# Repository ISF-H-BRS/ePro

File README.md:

# ePro: Secret Messages

## Introduction
ePro (short for entry-level project) was a series of introduction courses offered by Bonn-Rhein-Sieg University of Applied Sciences starting in 2010.

One of these courses, named "Secret Messages", aimed to give first-semester students a practical introduction to the field of data transmission, from the most low-level concepts, such as logical voltage levels, over bus systems like UART, SPI and I²C up to higher-level concepts, such as protocol stacks and data encryption.

This repository contains schematics, PCB layout and firmware for a circuit board originally developed during an internship project in the summer of 2010 to support this course beginning later that year. These devices, based on an ATmega32 microcontroller, can communicate over any of the three aforementioned interfaces and exchange messages using a very simple encryption scheme. All signals are exposed via pin headers for analysis by means of oscilloscope and/or bus sniffer.

The message to be transmitted can be selected from a built-in database of famous quotations through a pin-protected administration menu where also the encryption key can be set. The goal of the project was for every team to analyze the data transmitted over the chosen interface, decipher the message and document their findings along the way.

Unfortunately the ePro courses were canceled with the introduction of a new curriculum some years ago. This repository is provided in the hope that the circuit boards developed back in 2010 might still find some use in similar academic projects in the future.

## License
The source code for the firmware is licensed under the terms of the GNU General Public License (GPL). The schematics and layout files are licensed under the terms of the Creative Commons Attribution-ShareAlike International Public License (CC BY-SA). See COPYING in the respective subdirectories for details.

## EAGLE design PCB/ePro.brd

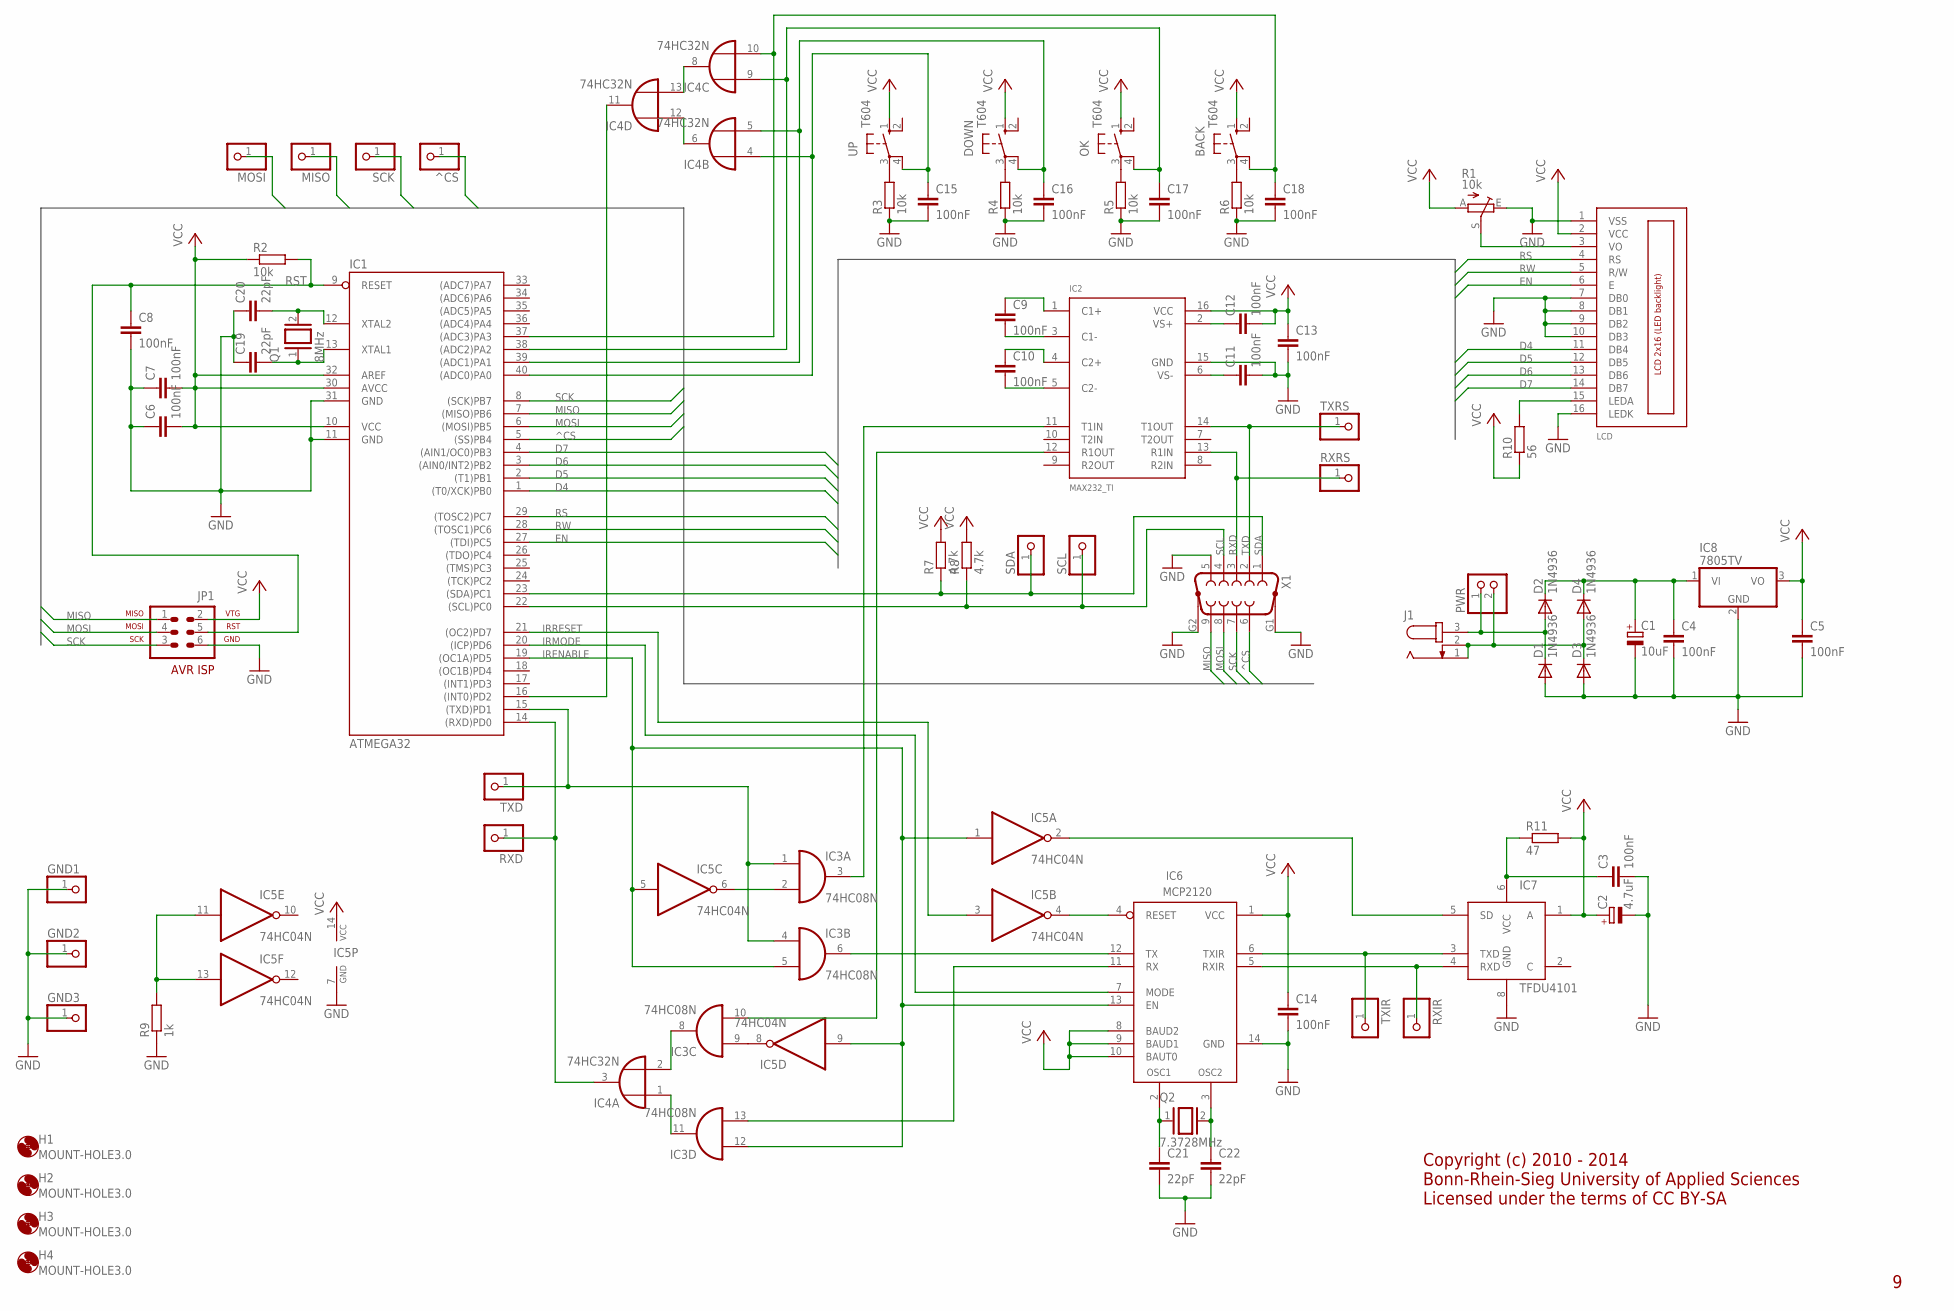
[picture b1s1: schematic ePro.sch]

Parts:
BACK: T604; T602/604
C1: 10uF; B45181B
C2: 4.7uF; B45181B
C3, C4, C5, C6, C7, C8, C9, C10, C11, C12, C13, C14, C15, C16, C17, C18: 100nF; C025-024X044
C19, C20, C21, C22: 22pF; C025-024X044
D1, D2, D3, D4: 1N4936; DO41-10
DOWN: T604; T602/604
GND1, GND2, GND3: PINHD-1X1; 1X01
H1, H2, H3, H4: MOUNT-HOLE3.0; 3,0
IC1: ATMEGA32; DIL40
IC2: MAX232_TI; DIL16
IC3: 74HC08N; DIL14
IC4: 74HC32N; DIL14
IC5: 74HC04N; DIL14
IC6: MCP2120; DIL14
IC7: TFDU4101; U
IC8: 7805TV; TO220V
J1: JACK-PLUG1; SPC4078
JP1: AVR-ISP-6
LCD: LCD_2X16_SIL; HY-1602F
MISO: PINHD-1X1; 1X01
MOSI: PINHD-1X1; 1X01
OK: T604; T602/604
PWR: PINHD-1X2; 1X02
Q1: 8MHz; QS
Q2: 7.3728MHz; QS
R1: 10k; PT-10S
R2, R3, R4, R5, R6: 10k; 0204/7
R7, R8: 4.7k; 0204/7
R9: 1k; 0204/7
R10: 56; 0204/7
R11: 47; 0204/7
RXD: PINHD-1X1; 1X01
RXIR: PINHD-1X1; 1X01
RXRS: PINHD-1X1; 1X01
SCK: PINHD-1X1; 1X01
SCL: PINHD-1X1; 1X01
SDA: PINHD-1X1; 1X01
TXD: PINHD-1X1; 1X01
TXIR: PINHD-1X1; 1X01
TXRS: PINHD-1X1; 1X01
UP: T604; T602/604
X1: F09HP
^CS: PINHD-1X1; 1X01

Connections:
D4: IC1.1 ((T0/XCK)PB0), LCD.11 (DB4)
D5: IC1.2 ((T1)PB1), LCD.12 (DB5)
D6: IC1.3 ((AIN0/INT2)PB2), LCD.13 (DB6)
D7: IC1.4 ((AIN1/OC0)PB3), LCD.14 (DB7)
EN: IC1.27 ((TDI)PC5), LCD.6 (E)
GND: C1.-, C2.-, C3.2, C4.2, C5.2, C6.1, C7.1, C8.2, C11.2, C13.2, C14.2, C15.2, C16.2, C17.2, C18.2, C19.1, C20.1, C21.2, C22.2, D1.A, D3.A, GND1.1, GND2.1, GND3.1, IC1.11 (GND), IC1.31 (GND), IC2.15 (GND), IC3.7 (GND), IC4.7 (GND), IC5.7 (GND), IC6.14 (GND), IC7.8 (GND), IC8.2 (GND), JP1.6, LCD.1 (VSS), LCD.7 (DB0), LCD.8 (DB1), LCD.9 (DB2), LCD.10 (DB3), LCD.16 (LEDK), R1.E, R3.1, R4.1, R5.1, R6.1, R9.1, X1.5, X1.G1, X1.G2
IRENABLE: IC1.19 ((OC1A)PD5), IC3.5 (I1), IC3.12 (I0), IC5.1 (I), IC5.5 (I), IC5.9 (I), IC6.13 (EN)
IRMODE: IC1.20 ((ICP)PD6), IC6.7 (MODE)
IRRESET: IC1.21 ((OC2)PD7), IC5.3 (I)
IRSHUTDOWN: IC5.2 (O), IC7.5 (SD)
MISO: IC1.7 ((MISO)PB6), JP1.1, MISO.1, X1.9
MOSI: IC1.6 ((MOSI)PB5), JP1.4, MOSI.1, X1.8
unnamed: IC1.15 ((TXD)PD1), IC3.1 (I0), IC3.4 (I0), TXD.1
unnamed: C15.1, IC1.40 ((ADC0)PA0), IC4.4 (I0), UP.4
unnamed: IC3.2 (I1), IC5.6 (O)
unnamed: IC4.6 (O), IC4.12 (I0)
unnamed: IC6.5 (RXIR), IC7.4 (RXD), RXIR.1
unnamed: C20.2, IC1.12 (XTAL2), Q1.2
unnamed: IC3.6 (O), IC6.12 (TX)
unnamed: C21.1, IC6.2 (OSC1), Q2.1
unnamed: IC6.6 (TXIR), IC7.3 (TXD), TXIR.1
unnamed: C16.1, DOWN.4, IC1.39 ((ADC1)PA1), IC4.5 (I1)
unnamed: C17.1, IC1.38 ((ADC2)PA2), IC4.9 (I0), OK.4
unnamed: IC2.12 (R1OUT), IC3.10 (I1)
unnamed: C11.1, IC2.6 (VS-)
unnamed: C3.1, IC7.6 (VCC), R11.1
unnamed: LCD.3 (VO), R1.S
unnamed: IC5.4 (O), IC6.4 (RESET)
unnamed: C22.1, IC6.3 (OSC2), Q2.2
unnamed: C10.2, IC2.5 (C2-)
unnamed: C19.2, IC1.13 (XTAL1), Q1.1
unnamed: IC3.13 (I1), IC6.11 (RX)
unnamed: IC3.9 (I0), IC5.8 (O)
unnamed: C1.+, C4.1, D2.C, D4.C, IC8.1 (VI)
unnamed: IC4.8 (O), IC4.13 (I1)
unnamed: C10.1, IC2.4 (C2+)
unnamed: LCD.15 (LEDA), R10.2
unnamed: IC3.8 (O), IC4.2 (I1)
unnamed: C9.2, IC2.3 (C1-)
unnamed: IC3.11 (O), IC4.1 (I0)
unnamed: IC1.14 ((RXD)PD0), IC4.3 (O), RXD.1
unnamed: C9.1, IC2.1 (C1+)
unnamed: C12.1, IC2.2 (VS+)
unnamed: D3.C, D4.A, J1.1, J1.2, PWR.2
unnamed: D1.C, D2.A, J1.3, PWR.1
unnamed: BACK.3, R6.2
unnamed: IC1.16 ((INT0)PD2), IC4.11 (O)
unnamed: BACK.4, C18.1, IC1.37 ((ADC3)PA3), IC4.10 (I1)
unnamed: IC2.11 (T1IN), IC3.3 (O)
unnamed: OK.3, R5.2
unnamed: DOWN.3, R4.2
unnamed: R3.2, UP.3
unnamed: IC5.11 (I), IC5.13 (I), R9.2
RS: IC1.29 ((TOSC2)PC7), LCD.4 (RS)
RST: C8.1, IC1.9 (RESET), JP1.5, R2.2
RW: IC1.28 ((TOSC1)PC6), LCD.5 (R/W)
RXD: IC2.13 (R1IN), RXRS.1, X1.3
SCK: IC1.8 ((SCK)PB7), JP1.3, SCK.1, X1.7
SCL: IC1.22 ((SCL)PC0), R8.1, SCL.1, X1.4
SDA: IC1.23 ((SDA)PC1), R7.1, SDA.1, X1.1
TXD: IC2.14 (T1OUT), TXRS.1, X1.2
VCC: BACK.1, C2.+, C5.1, C6.2, C7.2, C12.2, C13.1, C14.1, DOWN.1, IC1.10 (VCC), IC1.30 (AVCC), IC1.32 (AREF), IC2.16 (VCC), IC3.14 (VCC), IC4.14 (VCC), IC5.14 (VCC), IC6.1 (VCC), IC6.8 (BAUD2), IC6.9 (BAUD1), IC6.10 (BAUT0), IC7.1 (A), IC8.3 (VO), JP1.2, LCD.2 (VCC), OK.1, R1.A, R2.1, R7.2, R8.2, R10.1, R11.2, UP.1
^CS: IC1.5 ((SS)PB4), X1.6, ^CS.1

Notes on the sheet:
Copyright (c) 2010 - 2014 Bonn-Rhein-Sieg University of Applied Sciences Licensed under the terms of CC BY-SA

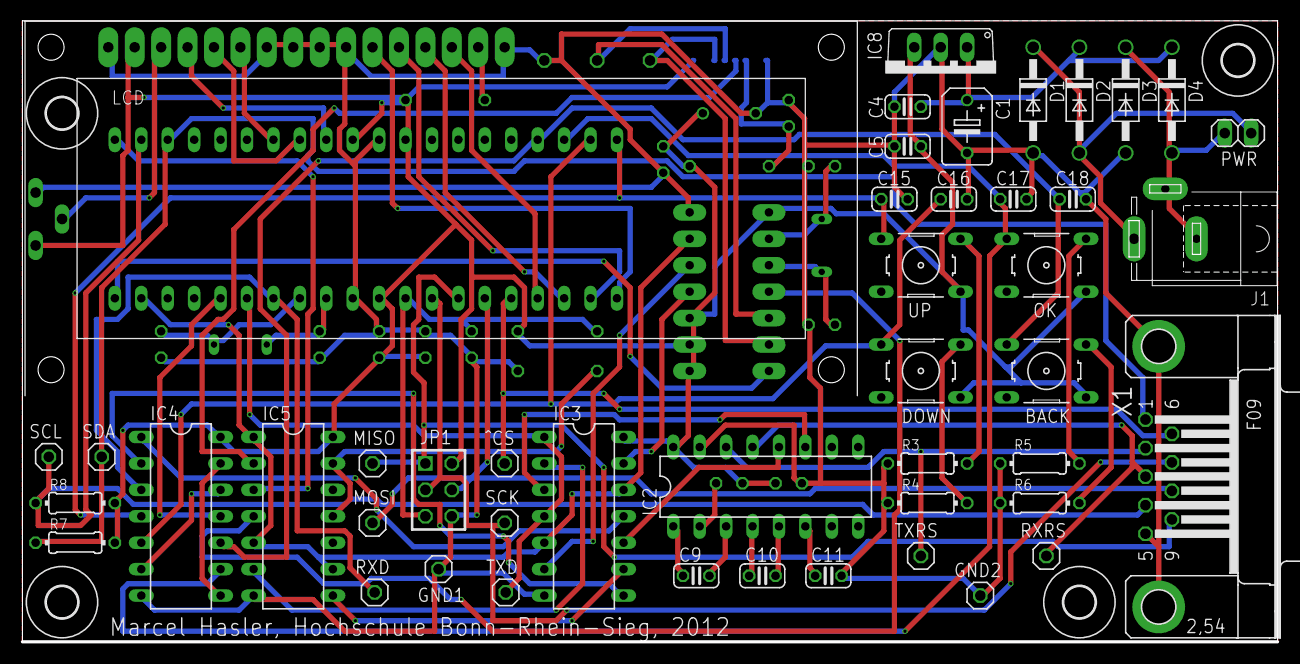
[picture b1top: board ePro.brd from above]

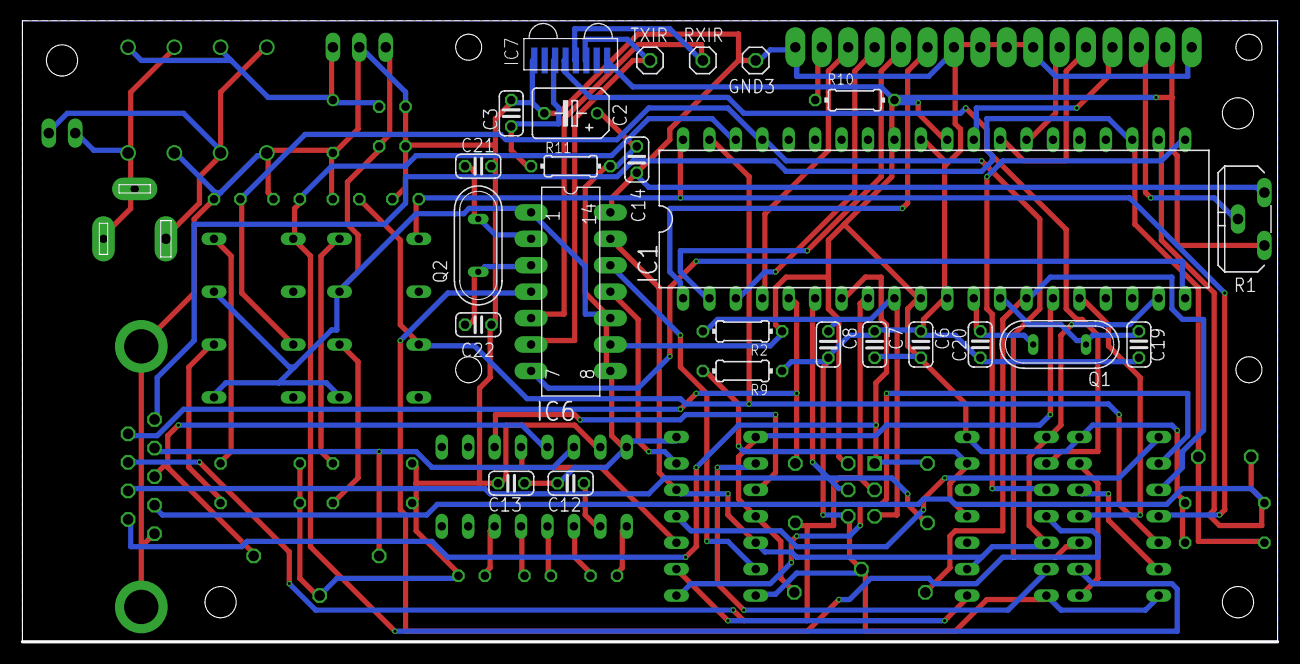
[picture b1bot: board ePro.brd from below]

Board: 2 copper layers, 120.7 x 59.5 mm, 75 parts (25 on the bottom side), 63 nets.

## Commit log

2024-05-26 Initial release.
